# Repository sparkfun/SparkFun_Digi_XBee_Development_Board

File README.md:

SparkFun Digi XBee® Development Board 
========================================

[*SparkFun Digi XBee® Development Board  (21636)*](https://www.sparkfun.com/products/21636)

The SparkFun Digi XBee® Development Board is designed to help you quickly and easily prototype low-power cellular IoT applications using the new Digi XBee 3 Low-Power LTE-M/NB-IoT and Digi XBee RR Pro modules. This board breaks out all the functionality of your XBee module and adds the ability to connect to the cellular network and (drumroll, please) GNSS. 

This is a "kitchen sink" development board that gives you access to the pin functionality of the XBee, includes two USB-C connectors for UART communication and firmware updates, a Qwiic connector for I<sup>2</sup>C capable sensors and peripherals, as well as Reset and D0 buttons and the ability to update firmware on the XBees that have cellular modules. There's also a JST port for a battery to allow your project to be more on the go.

Repository Contents
-------------------

* **/Documentation** - Data sheets, additional product information
* **/Hardware** - Eagle design files (.brd, .sch)
* **/Production** - Production panel files (.brd)

Documentation
--------------
* **[Hookup Guide](https://docs.sparkfun.com/SparkFun_Digi_XBee_Development_Board/)** - Basic hookup guide for the SparkFun Digi XBee® Development Board.

License Information
-------------------

This product is _**open source**_! 

Please review the LICENSE.md file for license information. 

If you have any questions or concerns on licensing, please contact technical support on our [SparkFun forums](https://forum.sparkfun.com/viewforum.php?f=152).

Distributed as-is; no warranty is given.

- Your friends at SparkFun.

_<COLLABORATION CREDIT>_

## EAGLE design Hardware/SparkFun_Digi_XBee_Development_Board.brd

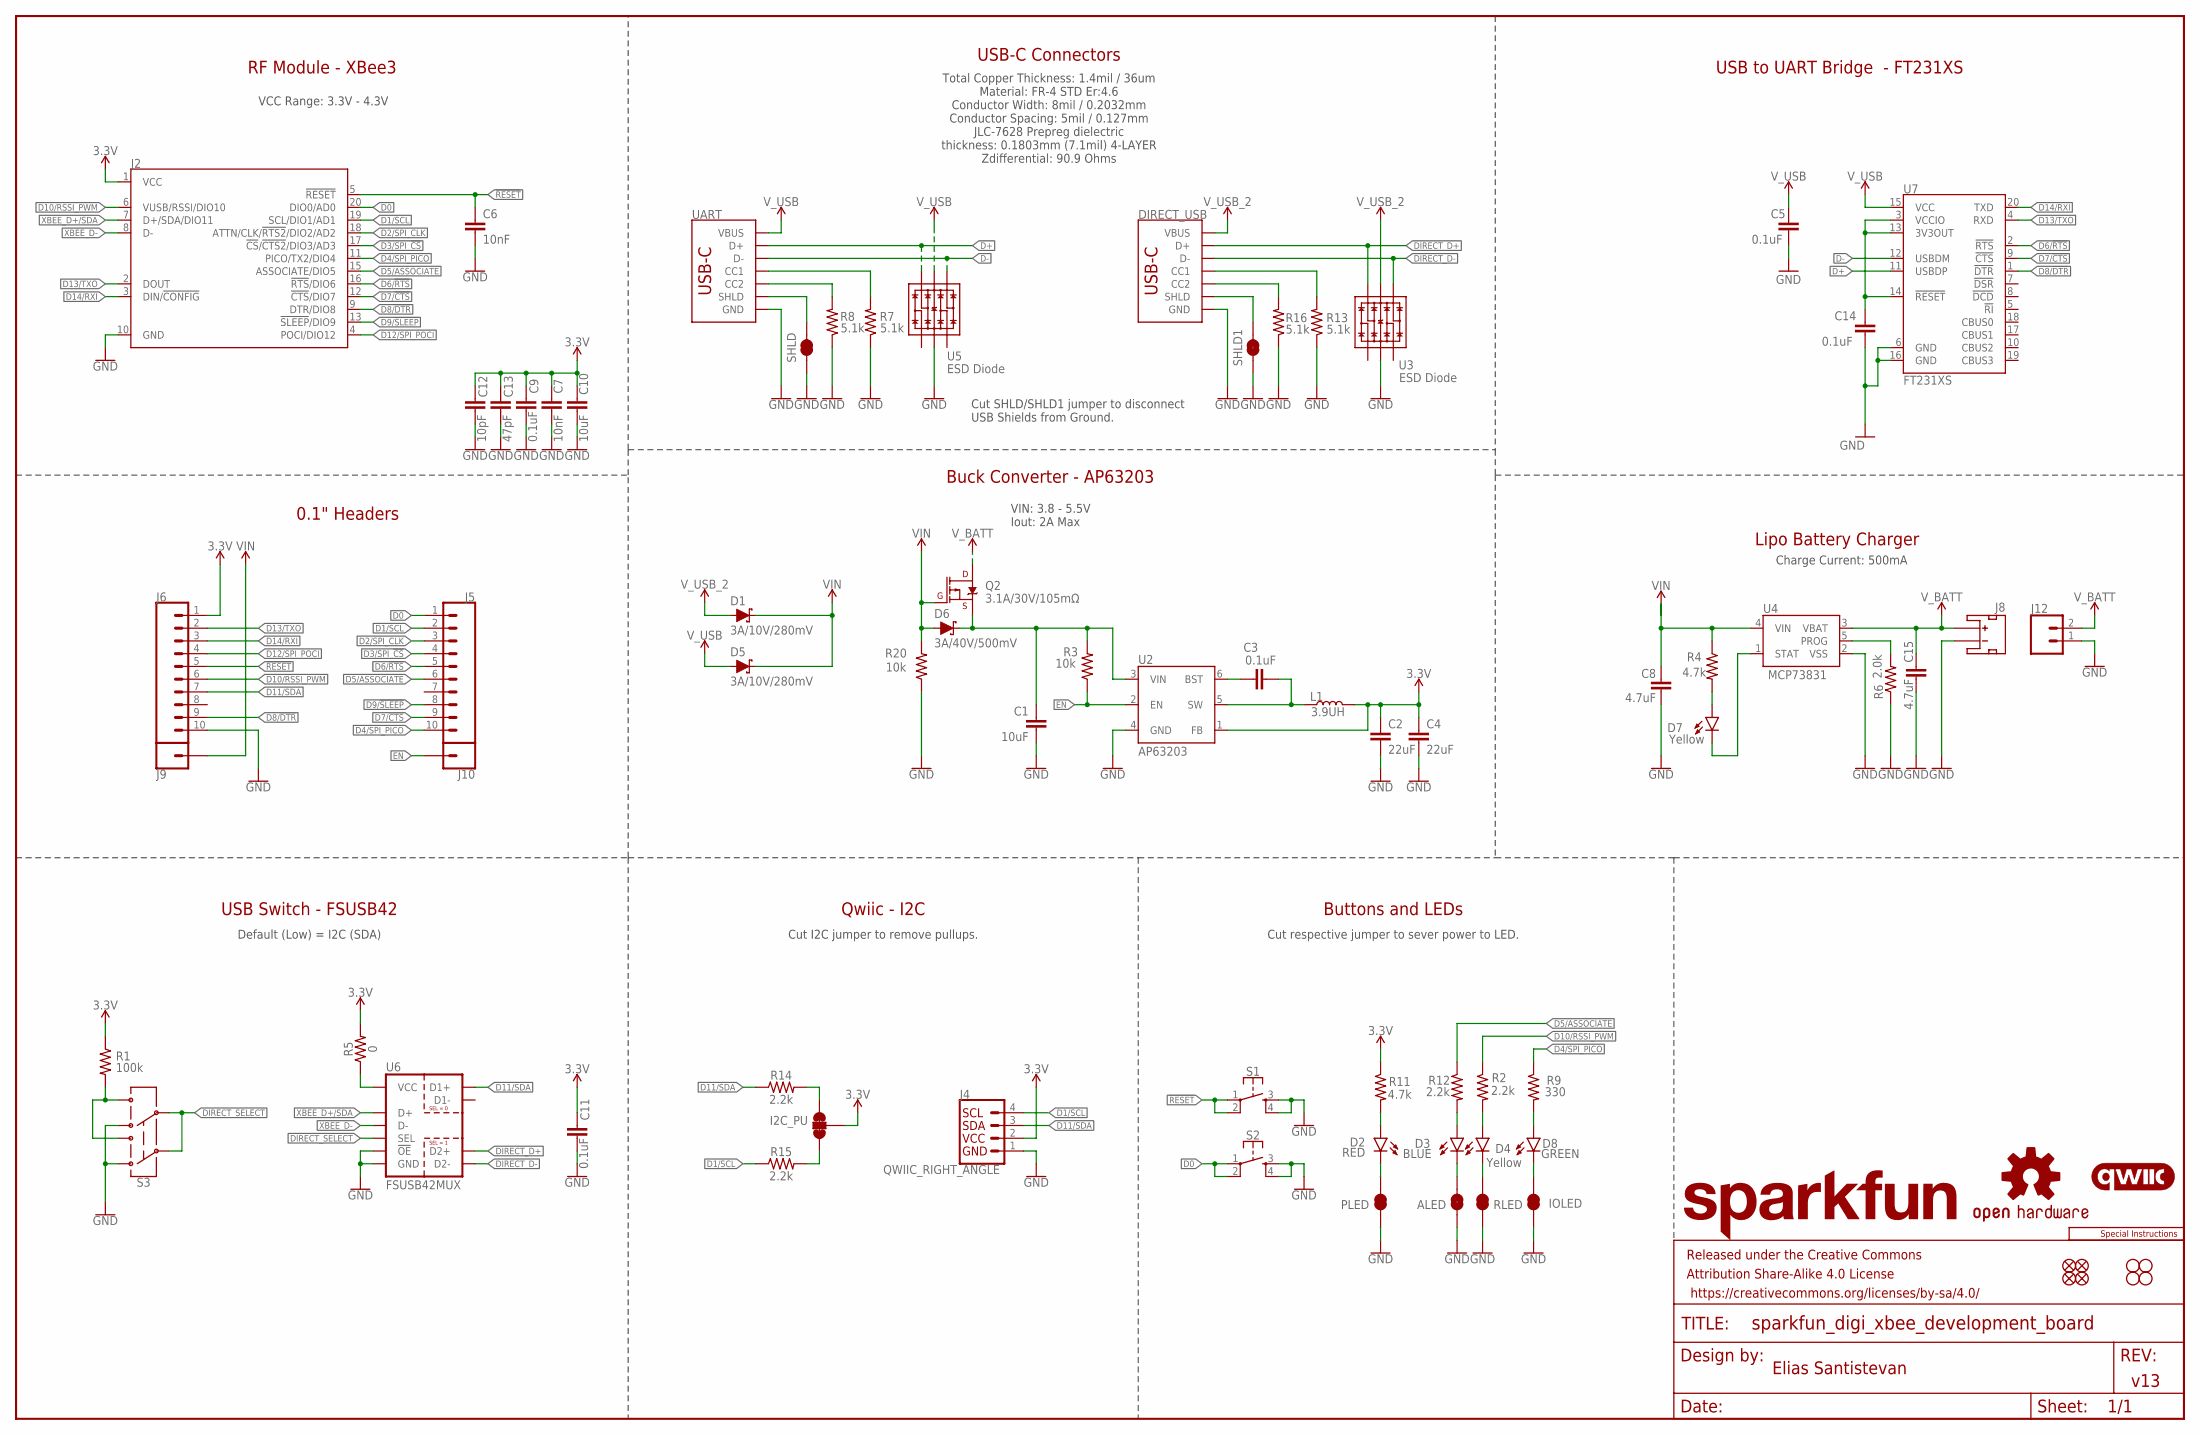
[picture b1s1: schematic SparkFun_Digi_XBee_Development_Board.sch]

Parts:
ALED: JUMPER-SMT_2_NC_TRACE_SILK; SMT-JUMPER_2_NC_TRACE_SILK
C1: 10uF; 1210
C2, C4: 22uF; 0603
C3, C5, C9, C11, C14: 0.1uF; 0603
C6, C7: 10nF; 0603
C8, C15: 4.7uF; 0603
C10: 10uF; 0603
C12: 10pF; 0603
C13: 47pF; 0603
D1, D5: 3A/10V/280mV; SOD-323
D2: RED; LED-0603
D3: BLUE; LED-0603
D4, D7: Yellow; LED-0603
D6: 3A/40V/500mV; SMA-DIODE
D8: GREEN; LED-0603
DIRECT_USB: USB Female Type C Connector; USB-C-16P-4LAYER-ISOLATED
FD1, FD2, FD3, FD4: FIDUCIAL1X2; FIDUCIAL-1X2
FRAME1: FRAME-LEDGER; CREATIVE_COMMONS
H1, H2, H3, H4: STAND-OFFTIGHT; STAND-OFF-TIGHT
I2C_PU: JUMPER-SMT_3_2-NC_TRACE_SILK; SMT-JUMPER_3_2-NC_TRACE_SILK
IOLED: JUMPER-SMT_2_NC_TRACE_SILK; SMT-JUMPER_2_NC_TRACE_SILK
J2: XBEE_UPDATEXBEE_SMD; XBEE3-SMD
J4: QWIIC_RIGHT_ANGLE; JST04_1MM_RA
J5, J6: CONN_10NO_SILK_PTH_FEMALE; 1X10_NO_SILK
J8: JST_2MM_MALE; JST-2-SMD
J9, J10: CONN_01PTH_NO_SILK_STAND; 1X01_NO_SILK_STAND
J12: CONN_021X02_NO_SILK; 1X02_NO_SILK
L1: 3.9UH; INDUCTOR_3.9UH
LOGO1: SFE_LOGO_NAME.2_INCH; SFE_LOGO_NAME_.2
LOGO2: OSHW-LOGOS; OSHW-LOGO-S
LOGO3: QWIIC_LOGO_5MM; QWIIC_5MM
LOGO5: SPECIAL_INSTRUCTIONS-ORDERING; ORDERING_INSTRUCTIONS
PLED: JUMPER-SMT_2_NC_TRACE_SILK; SMT-JUMPER_2_NC_TRACE_SILK
Q2: 3.1A/30V/105mΩ; SOT23-3
R1: 100k; 0603
R2, R12, R14, R15: 2.2k; 0603
R3, R20: 10k; 0603
R4, R11: 4.7k; 0603
R5: 0; 0603
R6: 2.0k; 0603
R7, R8, R13, R16: 5.1k; 0603
R9: 330; 0603
RLED: JUMPER-SMT_2_NC_TRACE_SILK; SMT-JUMPER_2_NC_TRACE_SILK
S1, S2: MOMENTARY-SWITCH-SPST-2-SMD-5.2MM-TALL; TACTILE_SWITCH_SMD_5.2MM
S3: SWITCH-DPDT-SMD-AYZ0202; SWITCH_DPDT_SMD_AYZ0202
SHLD, SHLD1: JUMPER-SMT_2_NC_TRACE_SILK; SMT-JUMPER_2_NC_TRACE_SILK
U2: AP63203; SOT23-6
U3, U5: ESD Diode; SOT-23-6
U4: MCP73831; SOT23-5
U6: FSUSB42MUX; MSOP10
U7: FT231XS; SSOP20_L
UART: USB Female Type C Connector; USB-C-16P-4LAYER-ISOLATED

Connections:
3.3V: C2.1, C4.1, C7.1, C9.1, C10.1, C11.1, C12.1, C13.1, I2C_PU.2, J2.1 (VCC), J4.2, J6.1, L1.P$2 (2), R1.1, R5.2, R11.1, U2.1 (FB)
!RESET!: C6.1, J2.5 (!RESET!), J6.5, S1.1, S1.2
ALED: ALED.2, D3.C
D0: J2.20 (DIO0/AD0), J5.1, S2.1, S2.2
D1/SCL: J2.19 (SCL/DIO1/AD1), J4.4, J5.2, R15.1
D2/SPI_CLK: J2.18 (ATTN/CLK/!RTS2!/DIO2/AD2), J5.3
D3/SPI_!CS!: J2.17 (!CS!/!CTS2!/DIO3/AD3), J5.4
D4/SPI_PICO: J2.11 (PICO/TX2/DIO4), J5.10, R9.1
D5/ASSOCIATE: J2.15 (ASSOCIATE/DIO5), J5.6, R12.1
D6/!RTS!: J2.16 (!RTS!/DIO6), J5.5, U7.2 (!RTS)
D7/!CTS!: J2.12 (!CTS!/DIO7), J5.9, U7.9 (!CTS)
D8/!DTR!: J2.9 (DTR/DIO8), J6.9, U7.1 (!DTR)
D9/!SLEEP!: J2.13 (!SLEEP!/DIO9), J5.8
D10/RSSI_PWM: J2.6 (VUSB/RSSI/DIO10), J6.6, R2.1
D11/SDA: J4.3, J6.7, R14.1, U6.7 (D1+)
D12/SPI_POCI: J2.4 (POCI/DIO12), J6.4
D13/TXO: J2.2 (DOUT), J6.2, U7.4 (RXD)
D14/RXI: J2.3 (DIN/!CONFIG!), J6.3, U7.20 (TXD)
D+: U5.6 (IO4), U7.11 (USBDP), UART.A6 (D+), UART.B6 (D+)
D-: U5.4 (IO3), U7.12 (USBDM), UART.A7 (D-), UART.B7 (D-)
DIRECT_D+: DIRECT_USB.A6 (D+), DIRECT_USB.B6 (D+), U3.6 (IO4), U6.9 (D2+)
DIRECT_D-: DIRECT_USB.A7 (D-), DIRECT_USB.B7 (D-), U3.4 (IO3), U6.8 (D2-)
DIRECT_SELECT: S3.2, S3.5, U6.2 (SEL)
EN: J10.1, R3.1, U2.2 (EN)
FIRMWARE: R1.2, S3.1, S3.4
GND: ALED.1, C1.2, C2.2, C4.2, C5.2, C6.2, C7.2, C8.2, C9.2, C10.2, C11.2, C12.2, C13.2, C14.2, C15.2, DIRECT_USB.GND, DIRECT_USB.GND2 (GND), IOLED.1, J2.10 (GND), J4.1, J6.10, J8.1 (-), J12.1, PLED.1, R6.1, R7.1, R8.1, R13.1, R16.1, R20.1, RLED.1, S1.3, S1.4, S2.3, S2.4, S3.3, S3.6, SHLD.1, SHLD1.1, U2.4 (GND), U3.2 (VSS), U4.2 (VSS), U5.2 (VSS), U6.5 (GND), U6.10 (!OE!), U7.6 (GND), U7.16 (GND), UART.GND, UART.GND2 (GND)
IOLED: D8.C, IOLED.2
unnamed: C3.1, U2.6 (BST)
unnamed: D4.A, R2.2
unnamed: R5.1, U6.1 (VCC)
unnamed: R8.2, UART.B5 (CC2)
unnamed: R7.2, UART.A5 (CC1)
unnamed: R6.2, U4.5 (PROG)
unnamed: D2.A, R11.2
unnamed: C3.2, L1.P$1 (1), U2.5 (SW)
unnamed: D7.C, U4.1 (STAT)
unnamed: D7.A, R4.2
unnamed: I2C_PU.3, R14.2
unnamed: D3.A, R12.2
unnamed: I2C_PU.1, R15.2
unnamed: DIRECT_USB.B5 (CC2), R16.2
unnamed: C1.1, D6.C, Q2.2 (S), R3.2, U2.3 (VIN)
unnamed: DIRECT_USB.A5 (CC1), R13.2
unnamed: D8.A, R9.2
unnamed: C14.1, U7.3 (VCCIO), U7.13 (3V3OUT), U7.14 (!RESET)
PLED: D2.C, PLED.2
RLED: D4.C, RLED.2
SHLD: SHLD.2, UART.SHLD1 (SHLD), UART.SHLD2 (SHLD), UART.SHLD3 (SHLD), UART.SHLD4 (SHLD), UART.SHLD5 (SHLD), UART.SHLD6 (SHLD), UART.SHLD7 (SHLD), UART.SHLD8 (SHLD)
SHLD1: DIRECT_USB.SHLD1 (SHLD), DIRECT_USB.SHLD2 (SHLD), DIRECT_USB.SHLD3 (SHLD), DIRECT_USB.SHLD4 (SHLD), DIRECT_USB.SHLD5 (SHLD), DIRECT_USB.SHLD6 (SHLD), DIRECT_USB.SHLD7 (SHLD), DIRECT_USB.SHLD8 (SHLD), SHLD1.2
VIN: C8.1, D1.C, D5.C, D6.A, J9.1, Q2.1 (G), R4.1, R20.2, U4.4 (VIN)
V_BATT: C15.1, J8.2 (+), J12.2, Q2.3 (D), U4.3 (VBAT)
V_USB: C5.1, D5.A, U5.5 (VCC), U7.15 (VCC), UART.VBUS1 (VBUS), UART.VBUS2 (VBUS)
V_USB_2: D1.A, DIRECT_USB.VBUS1 (VBUS), DIRECT_USB.VBUS2 (VBUS), U3.5 (VCC)
XBEE_D+/SDA: J2.7 (D+/SDA/DIO11), U6.3 (D+)
XBEE_D-: J2.8 (D-), U6.4 (D-)

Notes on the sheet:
VCC Range: 3.3V - 4.3V
USB to UART Bridge - FT231XS
Buck Converter - AP63203
Lipo Battery Charger
Cut SHLD/SHLD1 jumper to disconnect USB Shields from Ground.
Qwiic - I2C
v13
Elias Santistevan
USB Switch - FSUSB42
Default (Low) = I2C (SDA)
Buttons and LEDs
VIN: 3.8 - 5.5V Iout: 2A Max
USB-C Connectors
Cut I2C jumper to remove pullups.
Cut respective jumper to sever power to LED.
RF Module - XBee3
0.1" Headers
Charge Current: 500mA
Total Copper Thickness: 1.4mil / 36um Material: FR-4 STD Er:4.6 Conductor Width: 8mil / 0.2032mm Conductor Spacing: 5mil / 0.127mm JLC-7628 Prepreg dielectric thickness: 0.1803mm (7.1mil) 4-LAYER Zdifferential: 90.9 Ohms

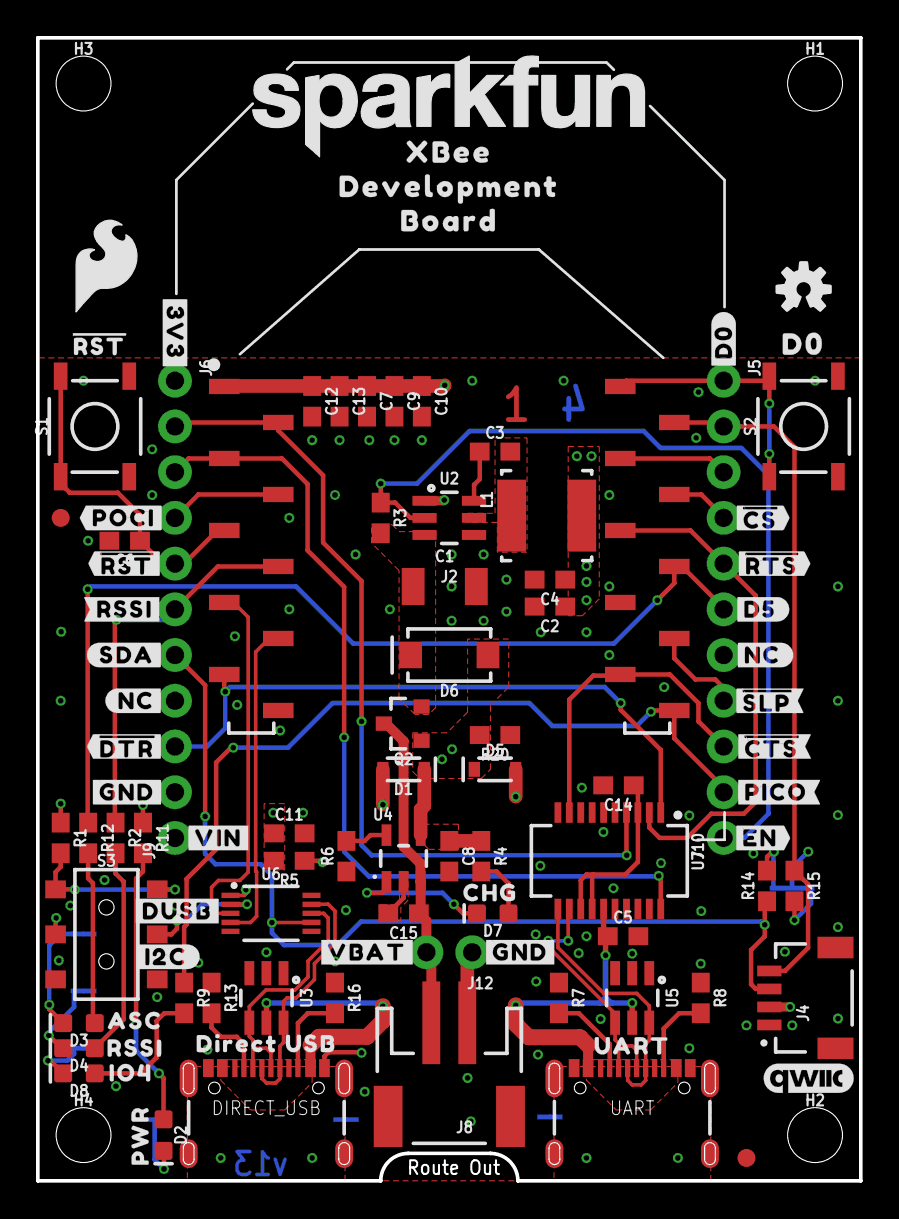
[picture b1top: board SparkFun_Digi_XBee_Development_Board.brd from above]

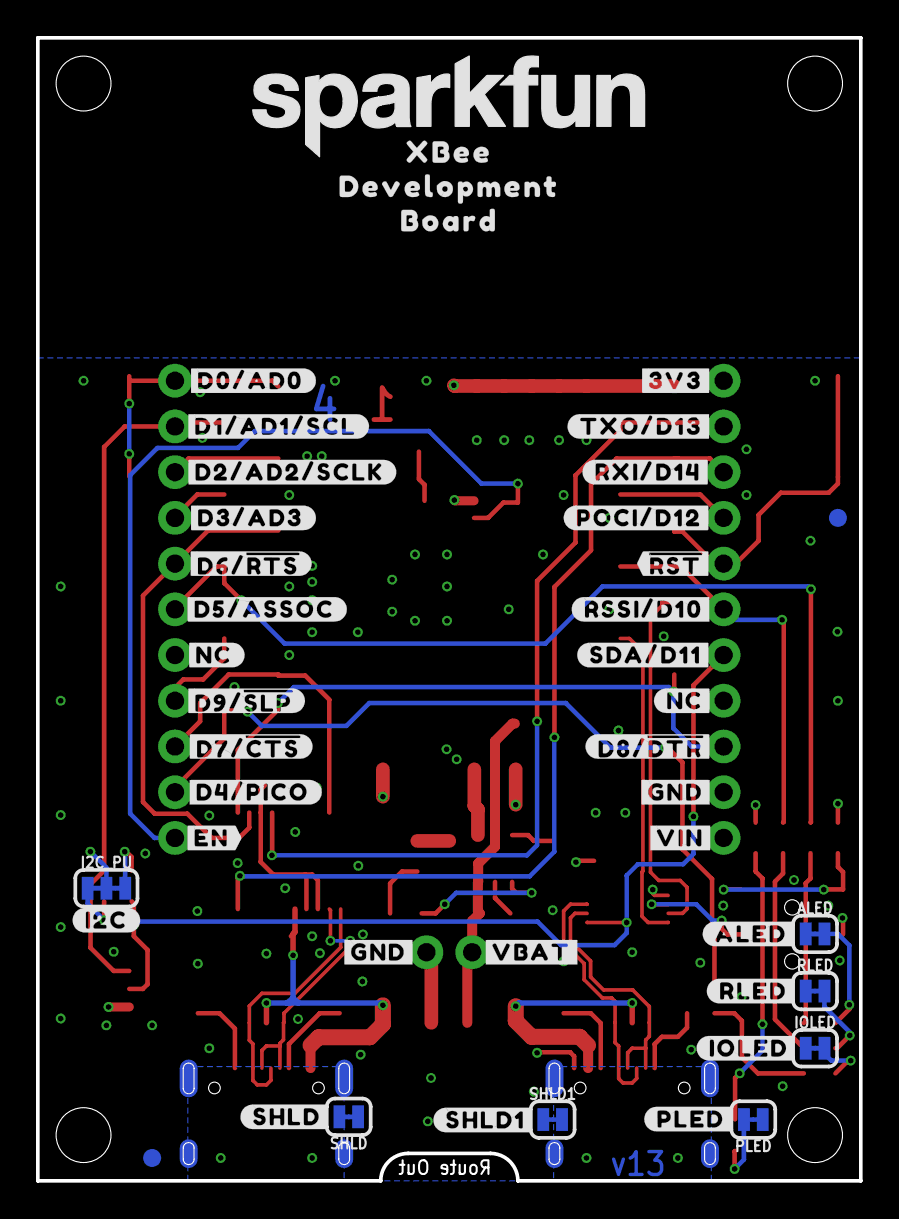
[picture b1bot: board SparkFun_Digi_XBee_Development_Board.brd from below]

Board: 4 copper layers, 45.7 x 63.5 mm, 150 parts (44 on the bottom side), 55 nets.

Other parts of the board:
U$1: #D2#AD2#SCLK#19
U$2, U$17: ##RST##15
U$3: ##CS##19
U$4: ##CTS##25
U$5: ##DTR##27
U$6: #D1#AD1#SCL#8
U$7: ##RTS##24
U$8, U$21: #EN#17
U$9, U$44: #3V3#1
U$10: #D0#18
U$11, U$37: #VBAT#5
U$12: #D3#AD3#22
U$13: #D4#PICO#24
U$14: #POCI#D12#24
U$15: #TXO#D13#13
U$16: #RXI#D14#15
U$18: #RSSI#D10#17
U$19: CHG47
U$20, U$25, U$38, U$45: #GND#0
U$22: #SDA#D11#8
U$23, U$50: XBEE339
U$24, U$67: #NC#1
U$26: #I2C#33
U$27: #ALED#21
U$28: #PICO#23
U$29: #POCI#23
U$30: #RST#30
U$31: #RSSI#16
U$32: #DUSB#31
U$33: IO46
U$34: #SDA#7
U$35: #SHLD#740
U$36: #SHLD1#741
U$39: #D5#3
U$40: D03
U$41, U$46: #VIN#4
U$42: PWR26
U$43: ASC32
U$47: ##SLP##27
U$48, U$66: #NC#3
U$49: #I2C#31
U$51, U$70: DEVELOPMENT1345
U$52, U$71: BOARD1346
U$53: #D8##DTR##27
U$54: #PLED#20
U$55: #D0#AD0#18
U$56: #D5#ASSOC#24
U$57: #D6##RTS##24
U$58: #D7##CTS##25
U$59: #IOLED#23
U$60: #D9##SLP##27
U$61: SFE_LOGO_FLAME_.2
U$62: RSSI31
U$63: SFE_LOGO_NAME_.2
U$64: #RLED#22
U$65: UART32
U$68: DIRECT_USB33

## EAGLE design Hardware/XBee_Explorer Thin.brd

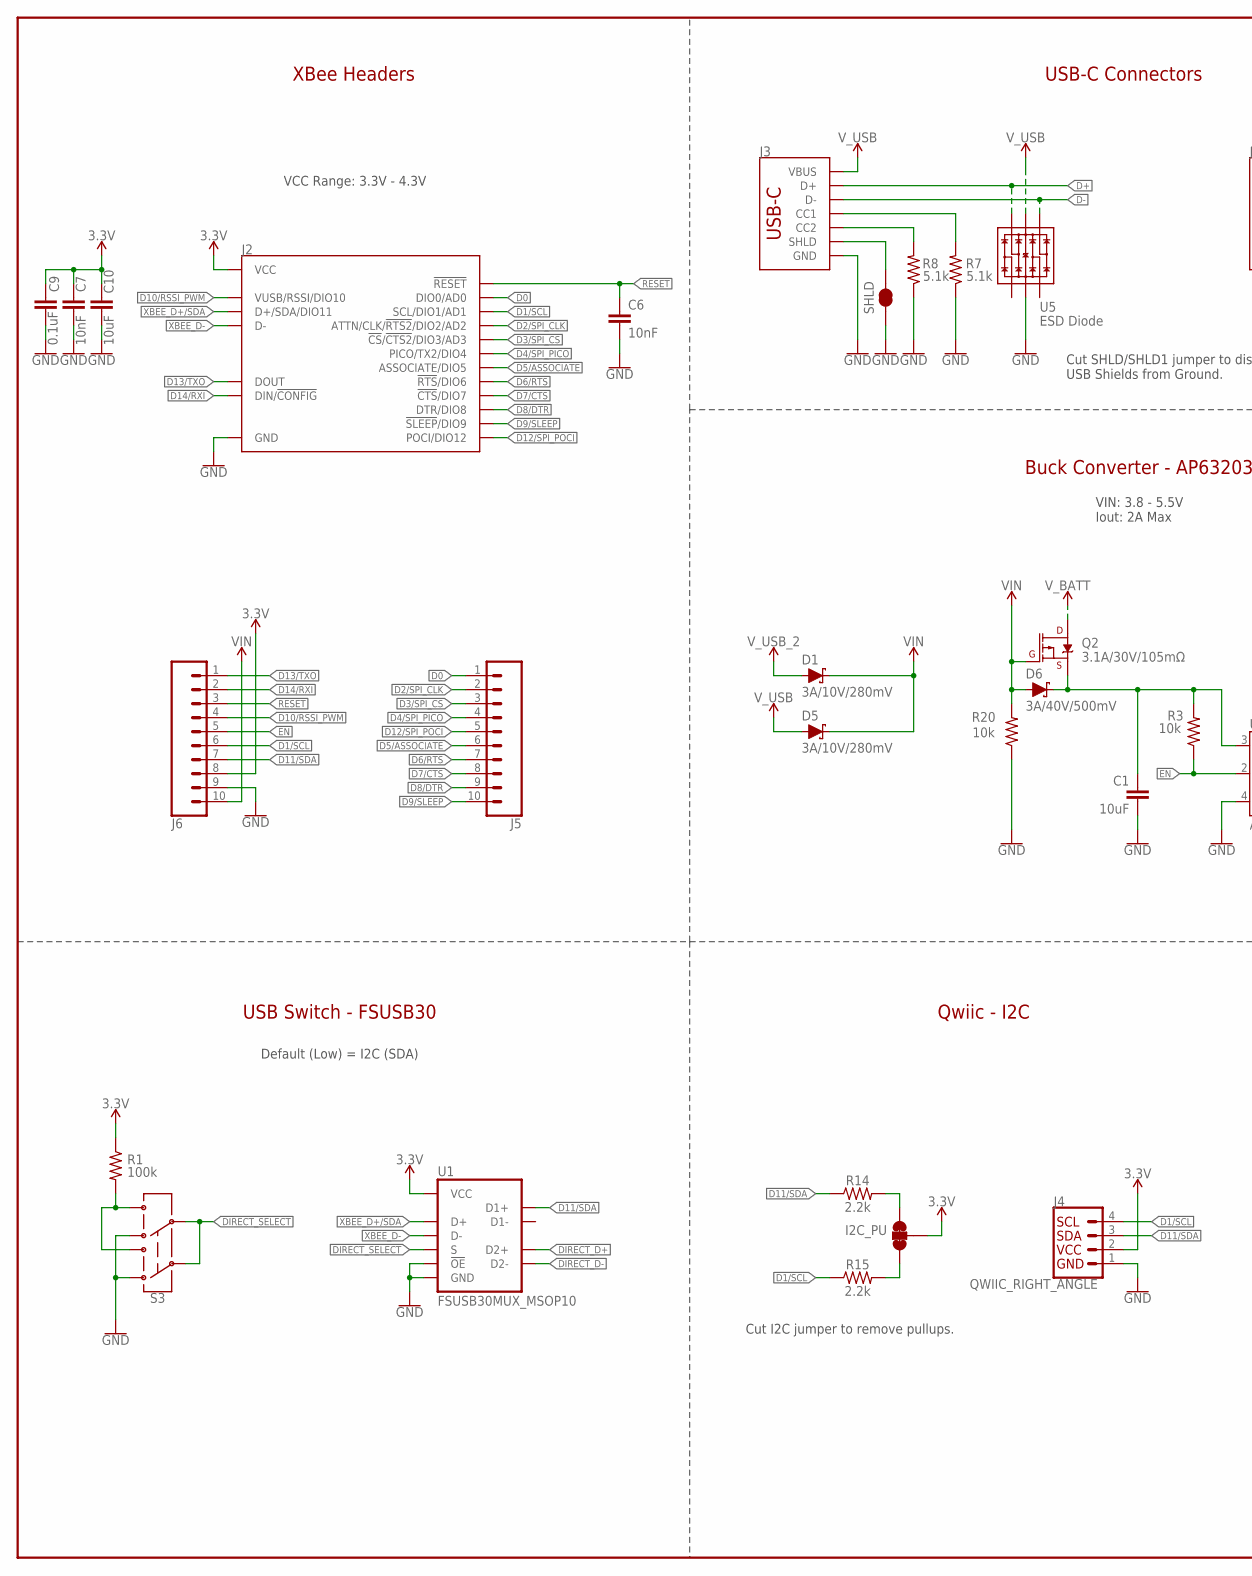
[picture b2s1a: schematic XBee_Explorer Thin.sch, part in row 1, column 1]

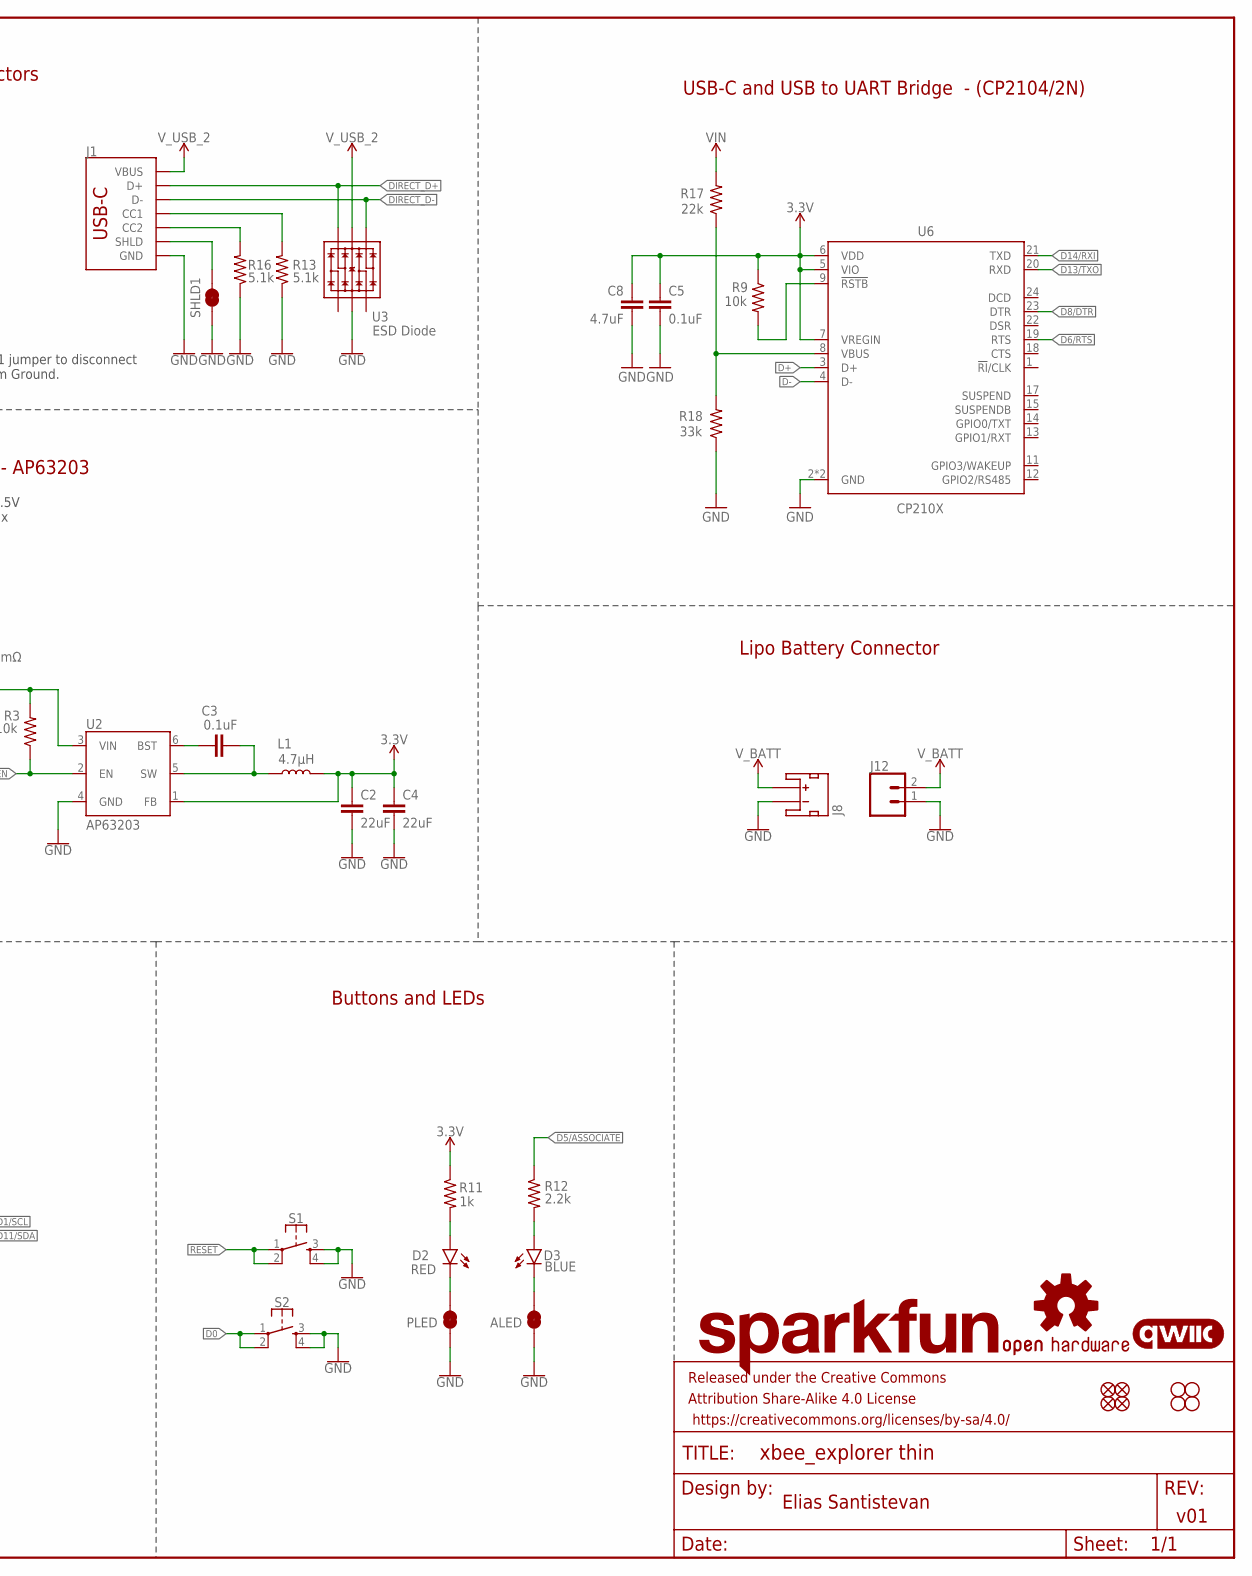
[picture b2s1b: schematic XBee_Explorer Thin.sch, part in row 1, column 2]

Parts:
ALED: JUMPER-SMT_2_NC_TRACE_SILK; SMT-JUMPER_2_NC_TRACE_SILK
C1: 10uF; 1210
C2, C4: 22uF; 0603
C3, C5, C9: 0.1uF; 0603
C6, C7: 10nF; 0603
C8: 4.7uF; 0603
C10: 10uF; 0603
D1, D5: 3A/10V/280mV; SOD-323
D2: RED; LED-0603
D3: BLUE; LED-0603
D6: 3A/40V/500mV; SMA-DIODE
FD1, FD2, FD3, FD4: FIDUCIAL1X2; FIDUCIAL-1X2
FRAME1: FRAME-LEDGER; CREATIVE_COMMONS
H1, H2, H3, H4: STAND-OFFTIGHT; STAND-OFF-TIGHT
I2C_PU: JUMPER-SMT_3_2-NC_TRACE_SILK; SMT-JUMPER_3_2-NC_TRACE_SILK
J1, J3: USB_C_2-LAYER_PADS; USB-C-16P-2LAYER-PADS
J2: XBEE_UPDATEXBEE_SMD; XBEE-SMD_SILK
J4: QWIIC_RIGHT_ANGLE; JST04_1MM_RA
J5, J6: CONN_10NO_SILK_PTH_FEMALE; 1X10_NO_SILK
J8: JST_2MM_MALE; JST-2-SMD
J12: CONN_021X02_NO_SILK; 1X02_NO_SILK
L1: 4.7μH; INDUCTOR_4X4MM
LOGO1: SFE_LOGO_NAME.1_INCH; SFE_LOGO_NAME_.1
LOGO2: OSHW-LOGOS; OSHW-LOGO-S
LOGO3: QWIIC_LOGO_5MM; QWIIC_5MM
PLED: JUMPER-SMT_2_NC_TRACE_SILK; SMT-JUMPER_2_NC_TRACE_SILK
Q2: 3.1A/30V/105mΩ; SOT23-3
R1: 100k; 0603
R3, R9, R20: 10k; 0603
R7, R8, R13, R16: 5.1k; 0603
R11: 1k; 0603
R12, R14, R15: 2.2k; 0603
R17: 22k; 0603
R18: 33k; 0603
S1, S2: MOMENTARY-SWITCH-SPST-2-SMD-5.2MM-TALL; TACTILE_SWITCH_SMD_5.2MM
S3: SWITCH-DPDT-SMD-AYZ0202; SWITCH_DPDT_SMD_AYZ0202
SHLD, SHLD1: JUMPER-SMT_2_NC_TRACE_SILK; SMT-JUMPER_2_NC_TRACE_SILK
U1: FSUSB30MUX_MSOP10; MSOP10
U2: AP63203; SOT23-6
U3, U5: ESD Diode; SOT-23-6
U6: CP210X; QFN24

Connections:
3.3V: C2.1, C4.1, C5.1, C7.1, C8.1, C9.1, C10.1, I2C_PU.2, J2.1 (VCC), J4.2, J6.8, L1.P$2 (2), R1.1, R9.1, R11.1, U1.10 (VCC), U2.1 (FB), U6.5 (VIO), U6.6 (VDD), U6.7 (VREGIN)
!RESET!: C6.1, J2.5 (!RESET!), J6.3, S1.1, S1.2
D0: J2.20 (DIO0/AD0), J5.1, S2.1, S2.2
D1/SCL: J2.19 (SCL/DIO1/AD1), J4.4, J6.6, R15.1
D2/SPI_CLK: J2.18 (ATTN/CLK/!RTS2!/DIO2/AD2), J5.2
D3/SPI_!CS!: J2.17 (!CS!/!CTS2!/DIO3/AD3), J5.3
D4/SPI_PICO: J2.11 (PICO/TX2/DIO4), J5.4
D5/ASSOCIATE: J2.15 (ASSOCIATE/DIO5), J5.6, R12.1
D6/!RTS!: J2.16 (!RTS!/DIO6), J5.7, U6.19 (RTS)
D7/!CTS!: J2.12 (!CTS!/DIO7), J5.8
D8/!DTR!: J2.9 (DTR/DIO8), J5.9, U6.23 (DTR)
D9/!SLEEP!: J2.13 (!SLEEP!/DIO9), J5.10
D10/RSSI_PWM: J2.6 (VUSB/RSSI/DIO10), J6.4
D11/SDA: J4.3, J6.7, R14.1, U1.2 (D1+)
D12/SPI_POCI: J2.4 (POCI/DIO12), J5.5
D13/TXO: J2.2 (DOUT), J6.1, U6.20 (RXD)
D14/RXI: J2.3 (DIN/!CONFIG!), J6.2, U6.21 (TXD)
D+: J3.A6 (D+), J3.B6 (D+), U5.6 (IO4), U6.3 (D+)
D-: J3.A7 (D-), J3.B7 (D-), U5.4 (IO3), U6.4 (D-)
DIRECT_D+: J1.A6 (D+), J1.B6 (D+), U1.3 (D2+), U3.6 (IO4)
DIRECT_D-: J1.A7 (D-), J1.B7 (D-), U1.7 (D2-), U3.4 (IO3)
DIRECT_SELECT: S3.2, S3.5, U1.1 (S)
EN: J6.5, R3.1, U2.2 (EN)
GND: ALED.1, C1.2, C2.2, C4.2, C5.2, C6.2, C7.2, C8.2, C9.2, C10.2, J1.GND, J1.GND2 (GND), J2.10 (GND), J3.GND, J3.GND2 (GND), J4.1, J6.9, J8.1 (-), J12.1, PLED.1, R7.1, R8.1, R13.1, R16.1, R18.1, R20.1, S1.3, S1.4, S2.3, S2.4, S3.3, S3.6, SHLD.1, SHLD1.1, U1.5 (GND), U1.9 (!OE!), U2.4 (GND), U3.2 (VSS), U5.2 (VSS), U6.2 (GND), U6.PAD (GND)
unnamed: C3.1, U2.6 (BST)
unnamed: R1.2, S3.1, S3.4
unnamed: J3.B5 (CC2), R8.2
unnamed: J3.A5 (CC1), R7.2
unnamed: D2.A, R11.2
unnamed: C3.2, L1.P$1 (1), U2.5 (SW)
unnamed: R9.2, U6.9 (!RSTB)
unnamed: R17.1, R18.2, U6.8 (VBUS)
unnamed: I2C_PU.3, R14.2
unnamed: D3.A, R12.2
unnamed: I2C_PU.1, R15.2
unnamed: J1.B5 (CC2), R16.2
unnamed: C1.1, D6.C, Q2.2 (S), R3.2, U2.3 (VIN)
unnamed: J1.A5 (CC1), R13.2
unnamed: ALED.2, D3.C
unnamed: D2.C, PLED.2
SHLD: J3.SHLD1 (SHLD), J3.SHLD2 (SHLD), J3.SHLD3 (SHLD), J3.SHLD4 (SHLD), SHLD.2
SHLD1: J1.SHLD1 (SHLD), J1.SHLD2 (SHLD), J1.SHLD3 (SHLD), J1.SHLD4 (SHLD), SHLD1.2
VIN: D1.C, D5.C, D6.A, J6.10, Q2.1 (G), R17.2, R20.2
V_BATT: J8.2 (+), J12.2, Q2.3 (D)
V_USB: D5.A, J3.VBUS1 (VBUS), J3.VBUS2 (VBUS), U5.5 (VCC)
V_USB_2: D1.A, J1.VBUS1 (VBUS), J1.VBUS2 (VBUS), U3.5 (VCC)
XBEE_D+/SDA: J2.7 (D+/SDA/DIO11), U1.4 (D+)
XBEE_D-: J2.8 (D-), U1.6 (D-)

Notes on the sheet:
VCC Range: 3.3V - 4.3V
USB-C and USB to UART Bridge - (CP2104/2N)
Buck Converter - AP63203
Lipo Battery Connector
Cut SHLD/SHLD1 jumper to disconnect USB Shields from Ground.
XBee Headers
Qwiic - I2C
v01
Elias Santistevan
USB Switch - FSUSB30
Default (Low) = I2C (SDA)
Buttons and LEDs
VIN: 3.8 - 5.5V Iout: 2A Max
USB-C Connectors
Cut I2C jumper to remove pullups.

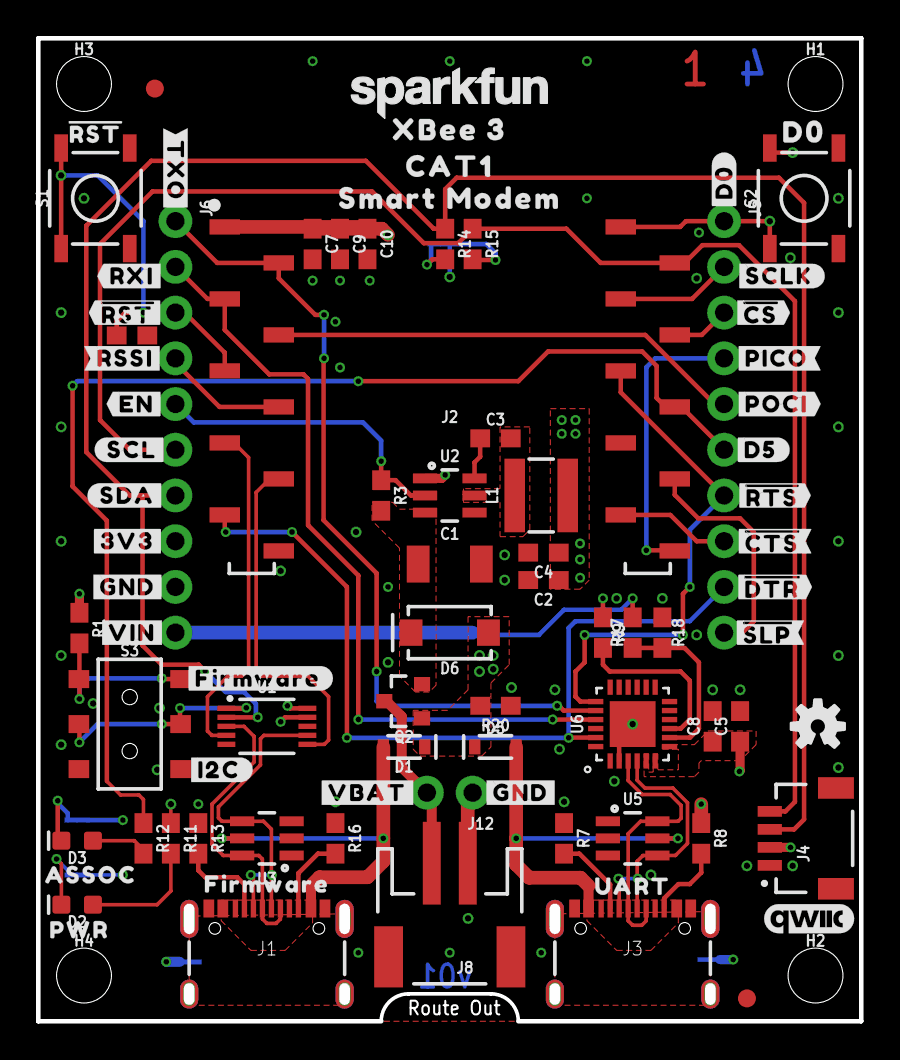
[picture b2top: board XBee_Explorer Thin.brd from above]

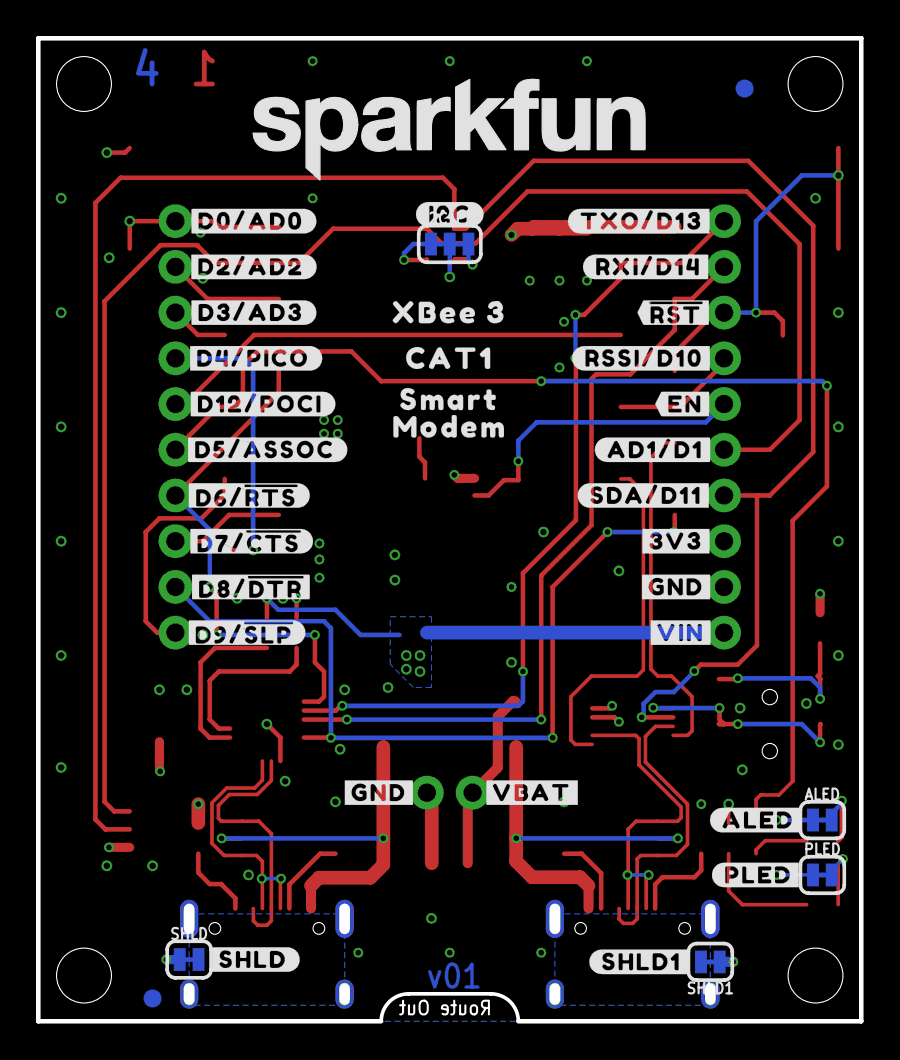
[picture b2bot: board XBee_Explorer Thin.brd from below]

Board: 4 copper layers, 45.7 x 54.6 mm, 129 parts (39 on the bottom side), 48 nets.

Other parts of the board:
U$1: #RXI#14
U$2, U$17: ##RST##15
U$3: ##CS##19
U$4: ##CTS##25
U$5: ##DTR##26
U$6: #D2#AD2#19
U$7: ##RTS##24
U$8: FIRMWARE29
U$9, U$44: #3V3#1
U$10: #D0#18
U$11, U$37: #VBAT#5
U$12: #D3#AD3#22
U$13: #D4#PICO#24
U$14: #D12#POCI#23
U$15: #TXO#D13#13
U$16: #RXI#D14#15
U$18: #RSSI#D10#17
U$19: #AD1#D1#7
U$20, U$25, U$38, U$45: #GND#0
U$21, U$24: #EN#17
U$22: #SDA#D11#8
U$23, U$53: XBEE_335
U$26: #I2C#33
U$27: #ALED#21
U$28: #PICO#23
U$29: #POCI#22
U$30: #RST#30
U$31: #RSSI#16
U$32: #SCL#6
U$33: #SCLK#18
U$34: #SDA#7
U$35: #SHLD#30
U$36: #SHLD1#31
U$39: #D5#3
U$40: D03
U$41, U$46: #VIN#4
U$42: PWR26
U$43: ASSOC27
U$47: ##SLP##27
U$48: #FIRMWARE#31
U$49: #I2C#31
U$50: #TXO#12
U$51: SMART_MODEM1337
U$52, U$61: CAT1336
U$54: #PLED#20
U$55: #D0#AD0#18
U$56: #D5#ASSOC#24
U$57: #D6##RTS##24
U$58: #D7##CTS##25
U$59: #D8##DTR##26
U$60: #D9##SLP##27
U$62: SMART1337
U$63: SFE_LOGO_NAME_.2
U$64: MODEM1338
U$65: UART32

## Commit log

2023-01-04 Adds higher current capable switching regulator
2023-01-05 Using new VREG, adds documentation for new VREG
2023-01-05 Removes unused design
2023-01-06 Updates schematic
2023-01-06 General placement of parts within the board
2023-01-06 Even better locations for the parts
2023-01-09 Routes some airwires
2023-01-09 Routes more air wires
2023-01-09 Finishes routing air wires - optimizations next
2023-01-09 Removes VIN from pin one one header and puts it at pin 10
    * Shifts all other nets up one to accommodate VIN
2023-01-09 Updates some of the routing
2023-01-09 Adds additional vias for 3.3V output
2023-01-09 Adds Measures
2023-01-10 Improves the ground pour significantly
2023-01-10 Few more improvements
2023-01-13 Adds labels
2023-01-13 Adds version
2023-01-13 Fixes various DRC issues
2023-01-16 Fixes various schematic issues
2023-01-16 Adds two layers and many stitching vias
2023-01-16 Adds many vias, rearranges some part placement for better performance/routing
2023-01-17 Adds more direct feeback trace for feedback pin on regulator
    * Restricts ground pour underneath the inductor (which still needs to be changed)
    * Updates USB lines to get closer to a 90 ohm impedance (8 mil, 6mil spacing)
    * Removes voltage divider on EN pin that was changing the UVLO threshold.
2023-01-17 Updates measures
2023-01-17 Adds "UART" silk for other USB connector
2023-01-17 Updates footprint to include module outline, increases size of board, moves buttons
2023-01-17 Moves some silk labels, approves some DRC
2023-01-17 Adds a few more stitching vias
2023-01-17 Runs the correct DRC with four layers
2023-01-17 Fixes mounting holes being off grid
2023-01-17 Replaces the only 0402 on the board with an 0603, replaces only 100k resistor with a 10k, fixes input/ouput labeling
2023-01-17 Fixes DRC issue
2023-01-17 Adds PROD-ID to Xbee module
2023-01-18 Moves resistor colliding with switch, adds via under UART to serial IC, adds "1,2,3,4" in their respective layer
    * Moves design to origin
2023-01-18 Adds text for LED jumpers
2023-01-18 Adds protos
2023-01-18 Renames board files
2023-01-18 Renames zip file with prototype gerbers
2023-01-18 Renames all files once again to include the "3" for XBee
2023-01-19 Updates xbee sybmol to include pin numbers
2023-01-27 Updates library to include a version of the module with silk
    * Replaces module in design with the silk-ed version
    * Extends board to be able to include the module's outline in silk
    * Moves buttons and through holes to fit new size
    * Changes name of the product to "Xbee 3 Dev Kit"
    * Moves switch to make space for new silk
    * Adds RSSI LED
2023-01-27 Adds silk to new LED and its' jumper
2023-01-27 NEW PINOUT - rearranges pinout to match module pinout directly
2023-01-27 Updates silk
2023-01-27 Updates a few labels
2023-02-02 Replaces USB-C connector with four layer footprint
2023-02-03 Updates title for USB-C section
2023-02-15 Fixes silk on modem and silk for certain through holes
    * Moves "VIN" and "EN" through holes
    * Moves the switch down because the above through holes moved
    * Shift the copper down to accommodate smaller XBee modules
    * Changes name to "Development Board"
2023-02-15 Moves resistor for LEDs so that they're grouped in a better configuration
2023-02-16 Fixes silk, aligns some text in the schematic, adds ordering instructions
2023-02-17 Fixes a number of labels
2023-02-17 Updates single PTH with new footprint
2023-02-24 Updates design to use the FT231XS instead of the CP2102N
2023-02-24 Adds new 3.9uH Inductor
2023-02-24 Fixes swapped labels on LED jumpers
2023-02-24 Fixes silk width on inductor, shifts part to correct keepout errors
2023-02-24 Adds a few more vias
2023-02-27 Updates inductor to one with a higher saturation rating
2023-02-27 Updates size of the silk on inductor, decreases dimension line
2023-02-27 Adds production files, shifts buttons down just a bit
2023-02-27 Adds new 2 x 3 panel
2023-02-28 Adds gerbers for new panel
2023-02-28 Renames gerbers to include version
2023-03-01 Updates XBee section with correct name
2023-04-10 Adding documentation
    GitHub Pages files
2023-04-11 Updates to github docs
2023-04-11 workflow files
2023-04-13 Adds LED and Charging circuit - all routed (but not optimized
2023-04-13 Some routing improvements
2023-04-14 Rolls version to v11 (applies to last commit)
    * Adds silk
2023-04-14 Changes silk on IOLED jumper
2023-04-17 Swaps yellow user LED for a green one
    * Improves copper pour
    * Fixes some whacky traces
2023-04-17 Adjusts 3.3V polygon
2023-04-17 Panelizes new board design
2023-04-17 Fixes the order of the capacitors
2023-04-18 Updates production panel
2023-07-27 Updating code
2023-07-27 Adding changes to main branch
2023-07-27 Update mkdocs.yml
    Adding redirect from index to introduction
2023-07-27 Updating for build
2023-07-28 Updates to page names
2023-07-28 Minor changes
2023-09-18 Fixing tables
2023-10-06 Powers FTDI with VUSB
2023-10-06 Moves ground pin nets to the bottom of the decoupling cap
2023-10-06 Updates production files
2023-10-06 Removes v11 production zip file, renames current zip file to include v12
2023-12-12 Periodic checkin
2023-12-12 Adding setuptools to build
2023-12-22 Major hardware overview update
2024-01-03 Hardware assembly and updates to overview
2024-01-03 Updating IO4
2024-01-03 Updating LED Jumper Header
2024-01-04 Updates to XBee Naming (trademark)
2024-01-05 Trademark changes
2024-01-08 Update hardware_overview.md per Eli notes
2024-01-08 Updating per Eli notes
2024-01-08 Deployed 214e45b with MkDocs version: 1.5.3
2024-03-18 Adds new FSUSB42 MUX switch
2024-03-18 Update to schematic text
2024-03-22 Adds text for USB calculation, nudges some things around for better pour
2024-03-22 Moves from 100 OHm to 0 OHm on VCC input for FUSB42
2024-03-22 Adds new panel - under new name unfortunately
2024-03-22 Adds version number to Production zip file, adds more notes to ordering instructions
2024-05-17 Deployed fdf4d5f with MkDocs version: 1.6.0
2026-06-03 Deployed ac9f1e4 with MkDocs version: 1.6.1

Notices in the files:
parts and their libraries:
SparkFun-Capacitors: Licensing: Creative Commons ShareAlike 4.0 International - https://creativecommons.org/licenses/by-sa/4.0
SparkFun-Aesthetics: Released under the Creative Commons Attribution Share-Alike 4.0 License
SparkFun-Aesthetics: https://creativecommons.org/licenses/by-sa/4.0
